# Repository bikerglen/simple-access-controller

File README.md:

# simple-access-controller
A very simple door access controller for a single RFID reader and a single door.

Complete details on my blog: https://bikerglen.com/blog/building-a-simple-rfid-door-access-controller/

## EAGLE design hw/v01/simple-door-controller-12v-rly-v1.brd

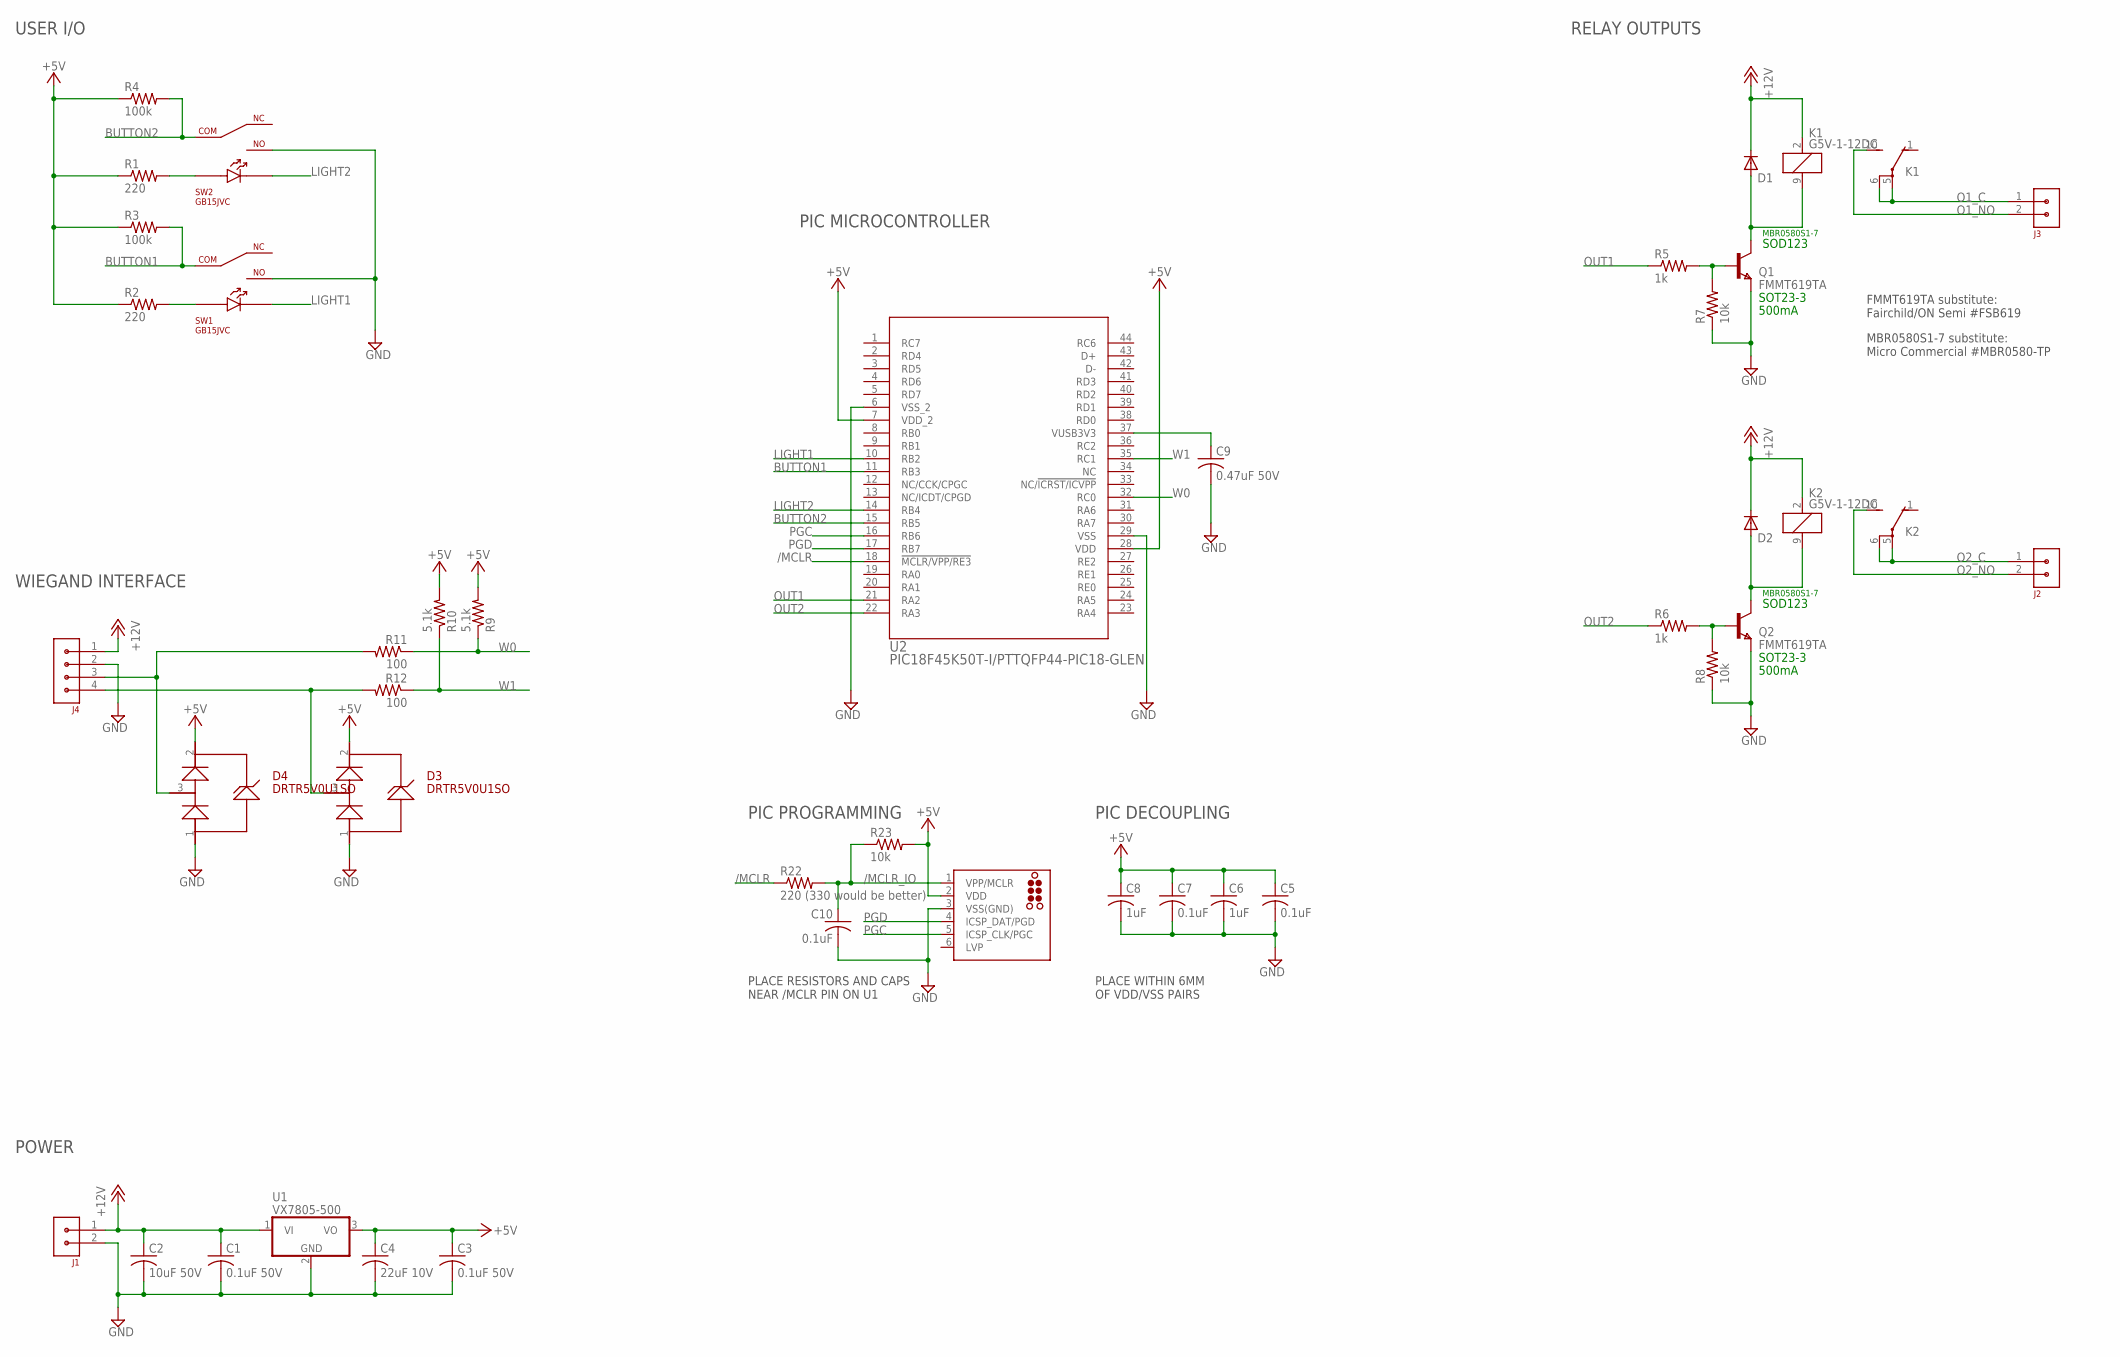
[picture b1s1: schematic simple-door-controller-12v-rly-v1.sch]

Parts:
C1, C3: 0.1uF 50V; C1206K; MFR_PART_NO C1206S104M5RACTU
C2: 10uF 50V; C1210K; MFR_PART_NO C1210C106K5RACTU
C4: 22uF 10V; C1206K; MFR_PART_NO C1206C226K8RAC7800
C5, C7, C10: 0.1uF; C0603K
C6, C8: 1uF; C0603K
C9: 0.47uF 50V; C1206K; MFR_PART_NO C1206C474K5RACTU
D1, D2: 1N4148W-TP; SOD123; MFR_PART_NO MBR0580S1-7
D3, D4: DRTR5V0U1SO; SOT23-3
DEBUG: TC2030-MCP-NL
J1, J2, J3: CON-3.81MM-1X2-PHOENIX; CON-PHOENIX-3.81-1X2-RA
J4: CON-3.81MM-1X4-PHOENIX-1803293; CON-PHOENIX-1803293-3.81-1X4
K1, K2: G5V-1-12DC; G5V1; MFR_PART_NO G5V-1-DC5
Q1, Q2: FMMT619TA; SOT-23; MFR_PART_NO FMMT619TA
R1, R2: 220; R0603
R3, R4: 100k; R0603
R5, R6: 1k; R0603; MFR_PART_NO CR1206-JW-102ELF
R7, R8: 10k; R0603; MFR_PART_NO CR1206-JW-102ELF
R9, R10: 5.1k; R0603; MFR_PART_NO CR1206-JW-102ELF
R11, R12: 100; R0603; MFR_PART_NO CR1206-JW-102ELF
R22: 220 (330 would be better); R0603
R23: 10k; R0603
SW1, SW2: GB15JVC; GB15JHC
U1: VX7805-500; CUI-78XX-500
U2: PIC18F45K50T-I/PTTQFP44-PIC18-GLEN; TQFP44-PIC18-GLEN

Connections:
+5V: C3.1, C4.1, C5.1, C6.1, C7.1, C8.1, D3.2, D4.2, DEBUG.2 (VDD), R1.1, R2.1, R3.1, R4.1, R9.2, R10.2, R23.2, U1.3 (VO), U2.7 (VDD_2), U2.28 (VDD)
+12V: C1.1, C2.1, D1.C, D2.C, J1.1, J4.1, K1.2 (1), K2.2 (1), U1.1 (VI)
/MCLR: R22.1, U2.18 (!MCLR/VPP/RE3)
/MCLR_IO: C10.1, DEBUG.1 (VPP/MCLR), R22.2, R23.1
BUTTON1: R3.2, SW1.5, U2.11 (RB3)
BUTTON2: R4.2, SW2.5, U2.15 (RB5)
GND: C1.2, C2.2, C3.2, C4.2, C5.2, C6.2, C7.2, C8.2, C9.2, C10.2, D3.1 (3), D4.1 (3), DEBUG.3 (VSS(GND)), J1.2, J4.2, Q1.2 (E), Q2.2 (E), R7.1, R8.1, SW1.4, SW2.4, U1.2 (GND), U2.6 (VSS_2), U2.29 (VSS)
LIGHT1: SW1.3, U2.10 (RB2)
LIGHT2: SW2.3, U2.14 (RB4)
unnamed: Q2.3 (B), R6.2, R8.2
unnamed: D2.A, K2.9 (2), Q2.1 (C)
unnamed: R1.2, SW2.1
unnamed: R2.2, SW1.1
unnamed: D3.3 (1), J4.4, R12.2
unnamed: D4.3 (1), J4.3, R11.2
unnamed: Q1.3 (B), R5.2, R7.2
unnamed: D1.A, K1.9 (2), Q1.1 (C)
O1_C: J3.1, K1.5, K1.6
O1_NO: J3.2, K1.10 (S)
O2_C: J2.1, K2.5, K2.6
O2_NO: J2.2, K2.10 (S)
OUT1: R5.1, U2.21 (RA2)
OUT2: R6.1, U2.22 (RA3)
PGC: DEBUG.5 (ICSP_CLK/PGC), U2.16 (RB6)
PGD: DEBUG.4 (ICSP_DAT/PGD), U2.17 (RB7)
VUSB: C9.1, U2.37 (VUSB3V3)
W0: R9.1, R11.1, U2.32 (RC0)
W1: R10.1, R12.1, U2.35 (RC1)

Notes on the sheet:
USER I/O
SOD123
SOT23-3
500mA
MBR0580S1-7
FMMT619TA substitute: Fairchild/ON Semi #FSB619
MBR0580S1-7 substitute: Micro Commercial #MBR0580-TP
WIEGAND INTERFACE
POWER
RELAY OUTPUTS
PIC DECOUPLING
PIC PROGRAMMING
PLACE WITHIN 6MM OF VDD/VSS PAIRS
PLACE RESISTORS AND CAPS NEAR /MCLR PIN ON U1
PIC MICROCONTROLLER

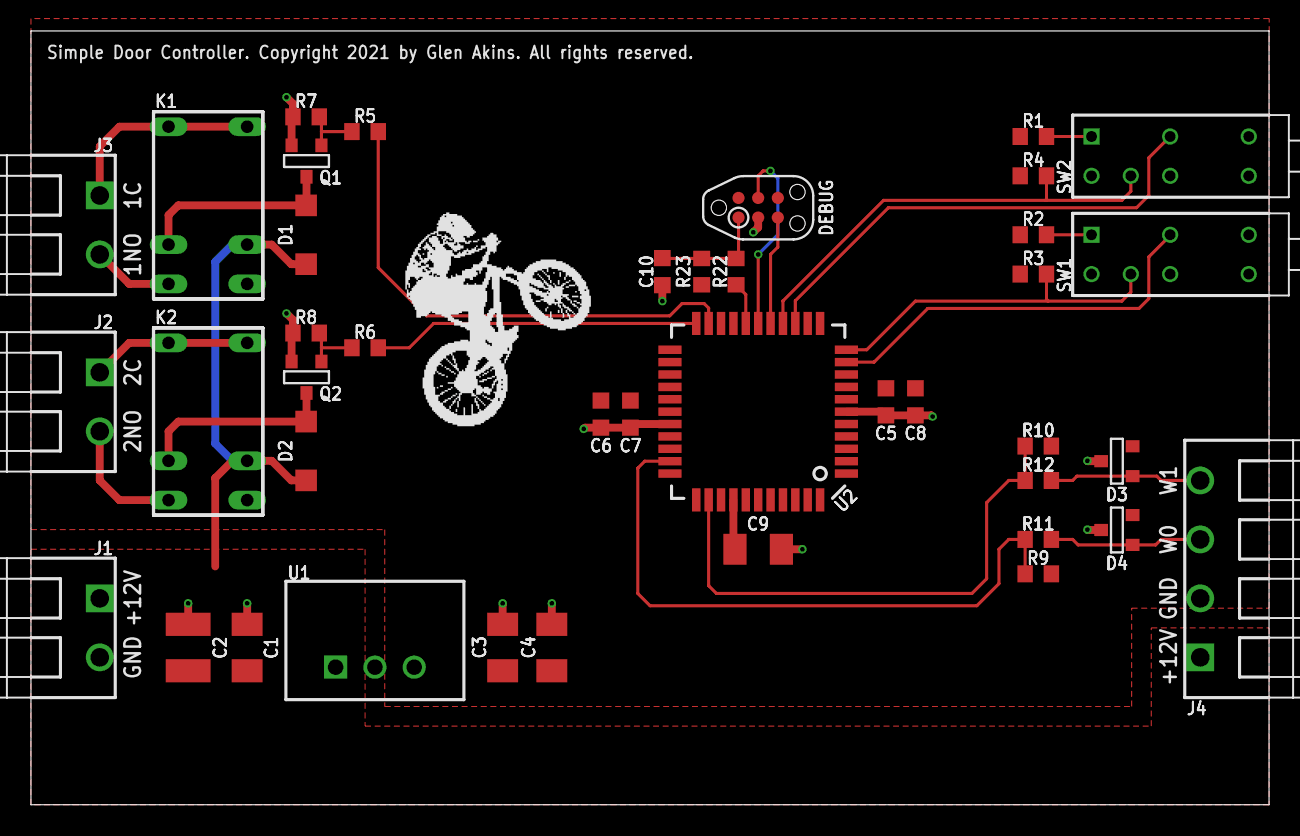
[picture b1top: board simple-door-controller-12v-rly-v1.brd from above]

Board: 2 copper layers, 80.0 x 50.0 mm, 41 parts (0 on the bottom side), 28 nets.

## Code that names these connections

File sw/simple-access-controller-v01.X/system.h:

#ifndef SYSTEM_H
#define SYSTEM_H

#include <xc.h>
#include <stdbool.h>

// 250 Hz timer 2 period value
// dec2hex(12e6/16/12/250-1)
#define TMR2_PERIOD 0xF9

// 250 Hz timer 0 load / reload value
// dec2hex(65535-12e6/16/250) = 0xF447
#define TMR0_RELOAD_VALUE 0xF447

// GPIO input pins
#define W0     (PORTCbits.RC0 ? 1 : 0)
#define W1     (PORTCbits.RC1 ? 1 : 0)
#define SW1    (PORTBbits.RB3 ? 0 : 1)
#define SW2    (PORTBbits.RB5 ? 0 : 1)

// GPIO output pints
#define RELAY1 LATAbits.LATA2
#define RELAY2 LATAbits.LATA3
#define LED1   LATBbits.LATB2
#define LED2   LATBbits.LATB4

// led states
#define LED_ON   0
#define LED_OFF  1

// relay states
#define RELAY_ON  1
#define RELAY_OFF 0

void SYSTEM_Initialize (void);
void TMR2_Initialize (void);
void TMR2_InterruptHandler (void);
void IOC_InterruptHandler (void);
void TMR0_Initialize (void);
void TMR0_Halt (void);
void TMR0_InterruptHandler (void);

#endif //SYSTEM_H

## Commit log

2021-08-13 initial checkin
2021-08-23 Update README.md
    Add URL

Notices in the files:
hw/v01/simple-door-controller-12v-rly-v1.brd:
Simple Door Controller. Copyright 2021 by Glen Akins. All rights reserved.
parts and their libraries:
tag-connect: ©2009 ROFA.cz - modified and updated by Robert Darlington ‹rdarlington@gmail.com›
PIC18F45K50: COPYRIGHT: Copyright (C) 2018 Accelerated Designs. All rights reserved
